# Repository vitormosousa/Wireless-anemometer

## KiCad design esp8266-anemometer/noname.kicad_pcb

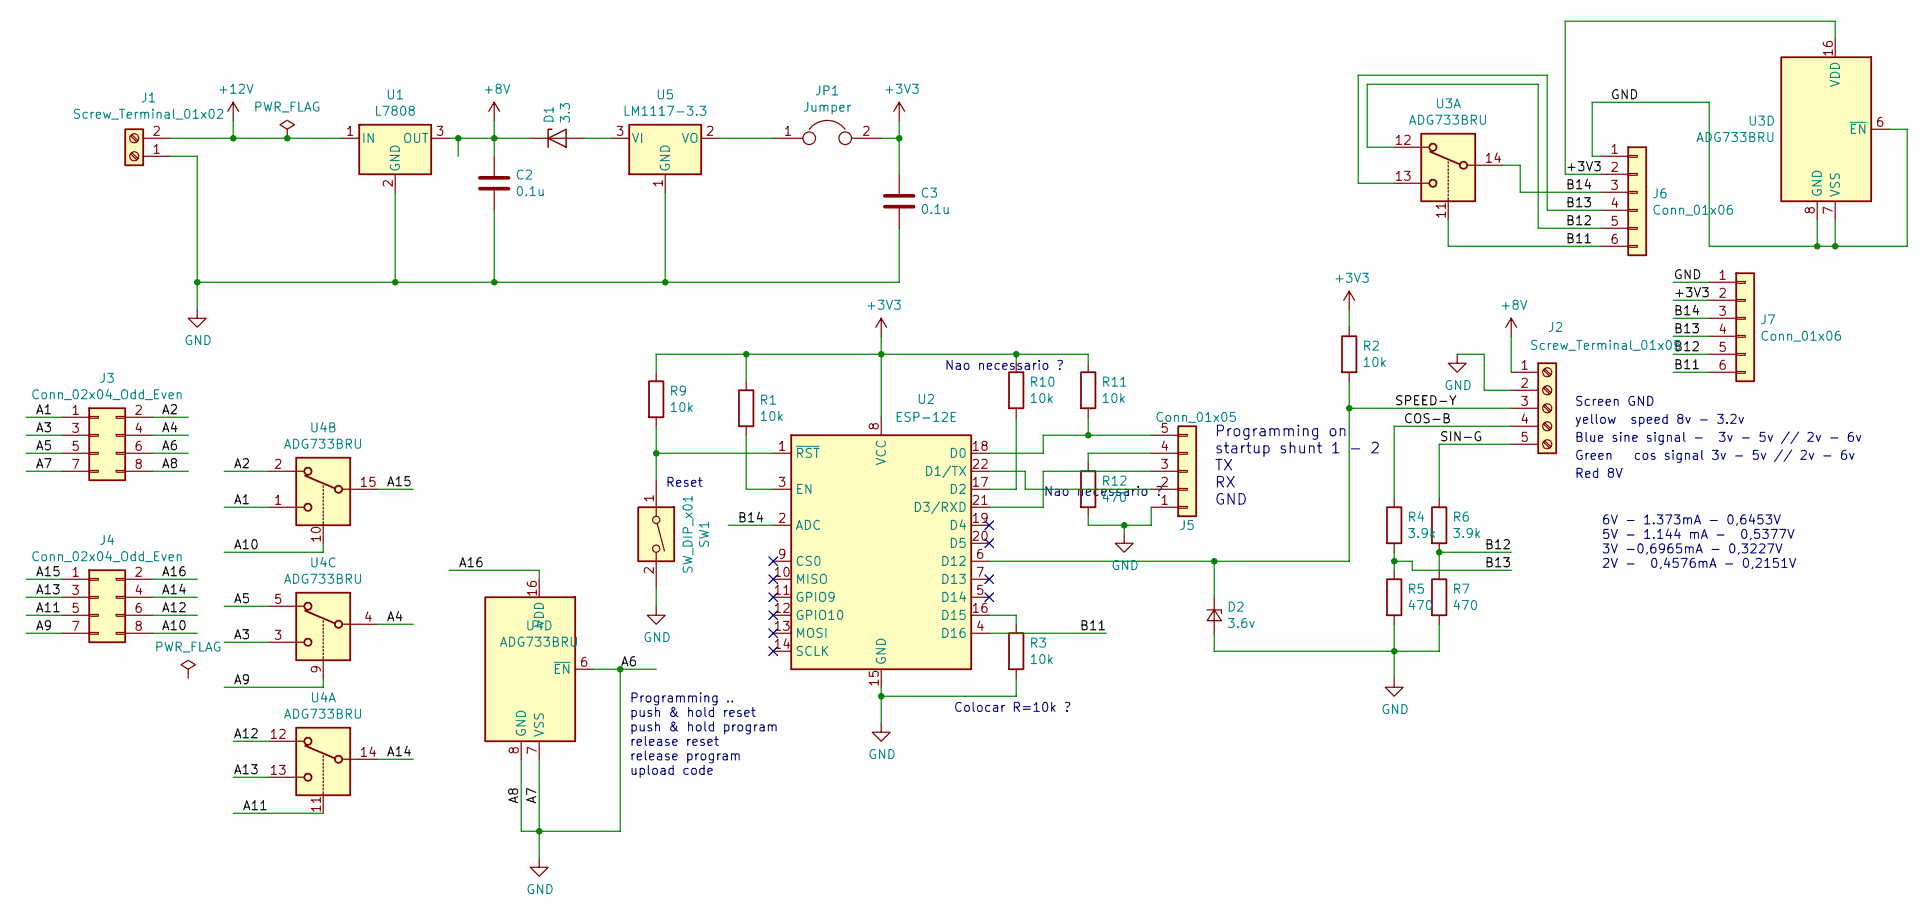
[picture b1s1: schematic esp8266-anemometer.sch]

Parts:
C2, C3: 0.1u; C_Disc_D4.3mm_W1.9mm_P5.00mm
D1: 3.3; D_DO-15_P10.16mm_Horizontal
D2: 3.6v; D_DO-15_P5.08mm_Vertical_AnodeUp
J1: Screw_Terminal_01x02; TerminalBlock_bornier-2_P5.08mm
J2: Screw_Terminal_01x05; TerminalBlock_bornier-5_P5.08mm
J3, J4: Conn_02x04_Odd_Even; PinHeader_2x04_P2.54mm_Vertical
J5: Conn_01x05; PinHeader_1x05_P2.54mm_Vertical
J6, J7: Conn_01x06; PinHeader_1x06_P2.54mm_Vertical
JP1: Jumper; PinHeader_1x02_P2.54mm_Vertical
R1, R10, R11: 10k; R_Axial_DIN0207_L6.3mm_D2.5mm_P10.16mm_Horizontal
R2, R3: 10k; R_Axial_DIN0204_L3.6mm_D1.6mm_P5.08mm_Vertical
R4, R6: 3.9k; R_Axial_DIN0207_L6.3mm_D2.5mm_P10.16mm_Horizontal
R5, R7, R12: 470; R_Axial_DIN0207_L6.3mm_D2.5mm_P10.16mm_Horizontal
R9: 10k; R_Axial_DIN0207_L6.3mm_D2.5mm_P15.24mm_Horizontal
SW1: SW_DIP_x01; SW_PUSH_6mm
U1: L7808; TO-220-3_Vertical
U2: ESP-12E
U3, U4: ADG733BRU; TSSOP-16_4.4x5mm_P0.65mm
U5: LM1117-3.3; TO-220-3_Vertical

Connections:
+8V: C2.1, D1.1 (K), J2.1, U1.3 (OUT)
+12V: J1.2, U1.1 (IN)
/A1: J3.1, U4.1
/A2: J3.2, U4.2
/A3: J3.3, U4.3
/A4: J3.4, U4.4
/A5: J3.5, U4.5
/A9: J4.7, U4.9
/A10: J4.8, U4.10
/A11: J4.5, U4.11
/A12: J4.6, U4.12
/A13: J4.3, U4.13
/A14: J4.4, U4.14
/A15: J4.1, U4.15
/A16: J4.2, U4.16 (VDD)
/B11: J6.6, J7.6, U2.4 (D16), U3.11
/B12: J6.5, J7.5, R6.2, R7.1, U3.12
/B13: J6.4, J7.4, R4.2, R5.1, U3.13
/B14: J6.3, J7.3, U2.2 (ADC), U3.14
/COS-B: J2.4, R4.1
/SIN-G: J2.5, R6.1
/SPEED-Y: D2.1 (K), J2.3, R2.2, U2.6 (D12)
GND: C2.2, C3.2, D2.2 (A), J1.1, J2.2, J3.6, J3.7, J3.8, J5.1, J6.1, J7.1, R3.2, R5.2, R7.2, R12.2, SW1.2, U1.2 (GND), U2.15 (GND), U3.6 (~EN), U3.7 (VSS), U3.8 (GND), U4.6 (~EN), U4.7 (VSS), U4.8 (GND), U5.1 (GND)
unnamed: D1.2 (A), U5.3 (VI)
unnamed: J5.2, U2.22 (D1/TX)
unnamed: J5.3, U2.21 (D3/RXD)
unnamed: J5.4, R12.1
unnamed: J5.5, R11.2, U2.18 (D0)
unnamed: JP1.1, U5.2 (VO)
unnamed: R1.2, U2.3 (EN)
unnamed: R3.1, U2.16 (D15)
unnamed: R9.2, SW1.1, U2.1 (~RST)
unnamed: R10.2, U2.17 (D2)

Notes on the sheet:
Red 8V
Screen GND
Blue sine signal - 3v - 5v // 2v - 6v
Green cos signal 3v - 5v // 2v - 6v
yellow speed 8v - 3.2v
Programming on startup shunt 1 - 2 TX RX GND
Programming .. push & hold reset push & hold program release reset release program upload code
Reset
Colocar R=10k ?
Nao necessario ?
6V - 1.373mA - 0,6453V 5V - 1.144 mA - 0,5377V 3V -0,6965mA - 0,3227V 2V - 0,4576mA - 0,2151V

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
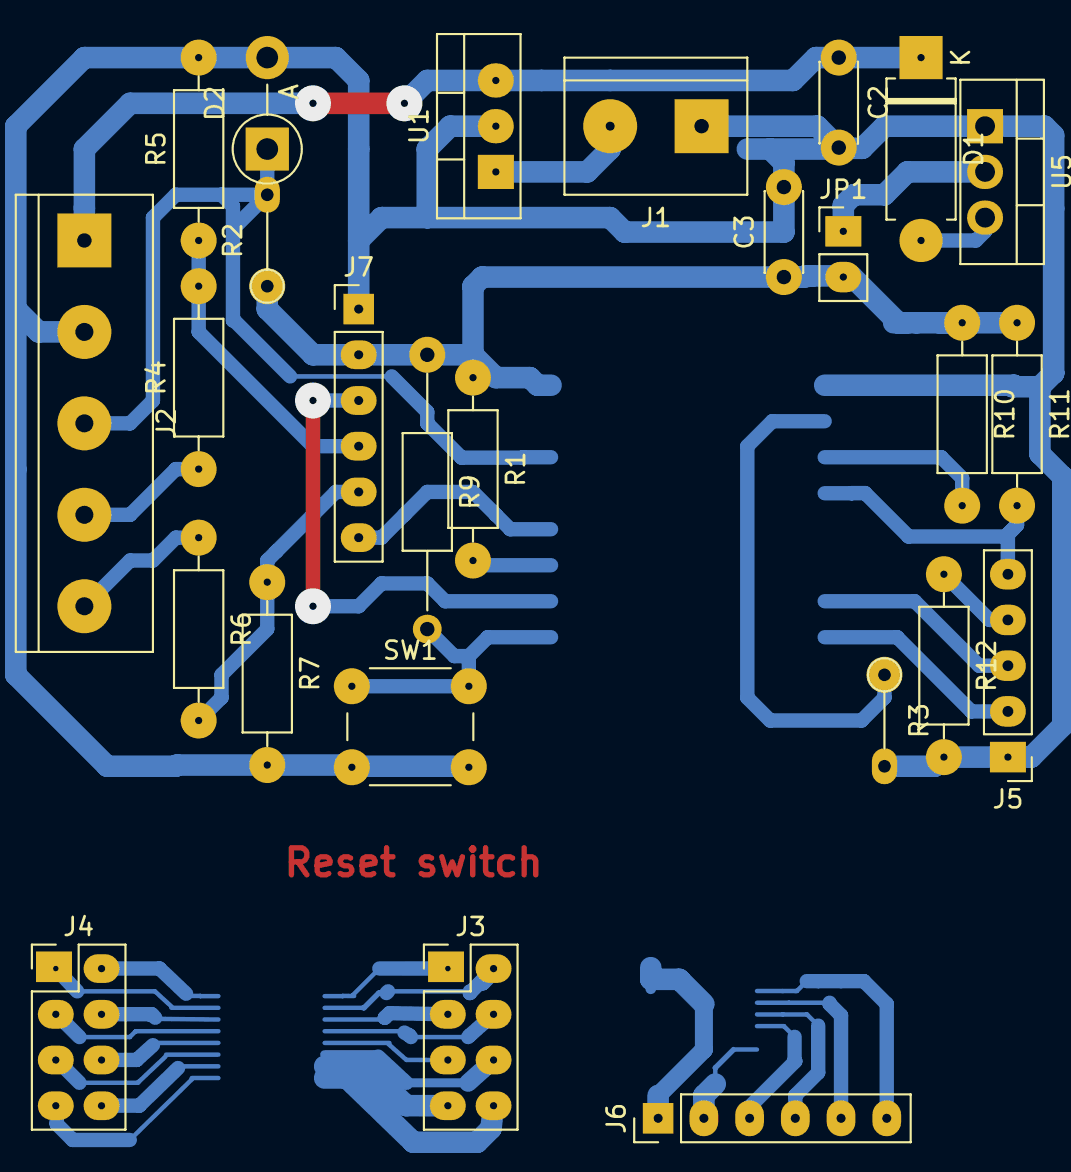
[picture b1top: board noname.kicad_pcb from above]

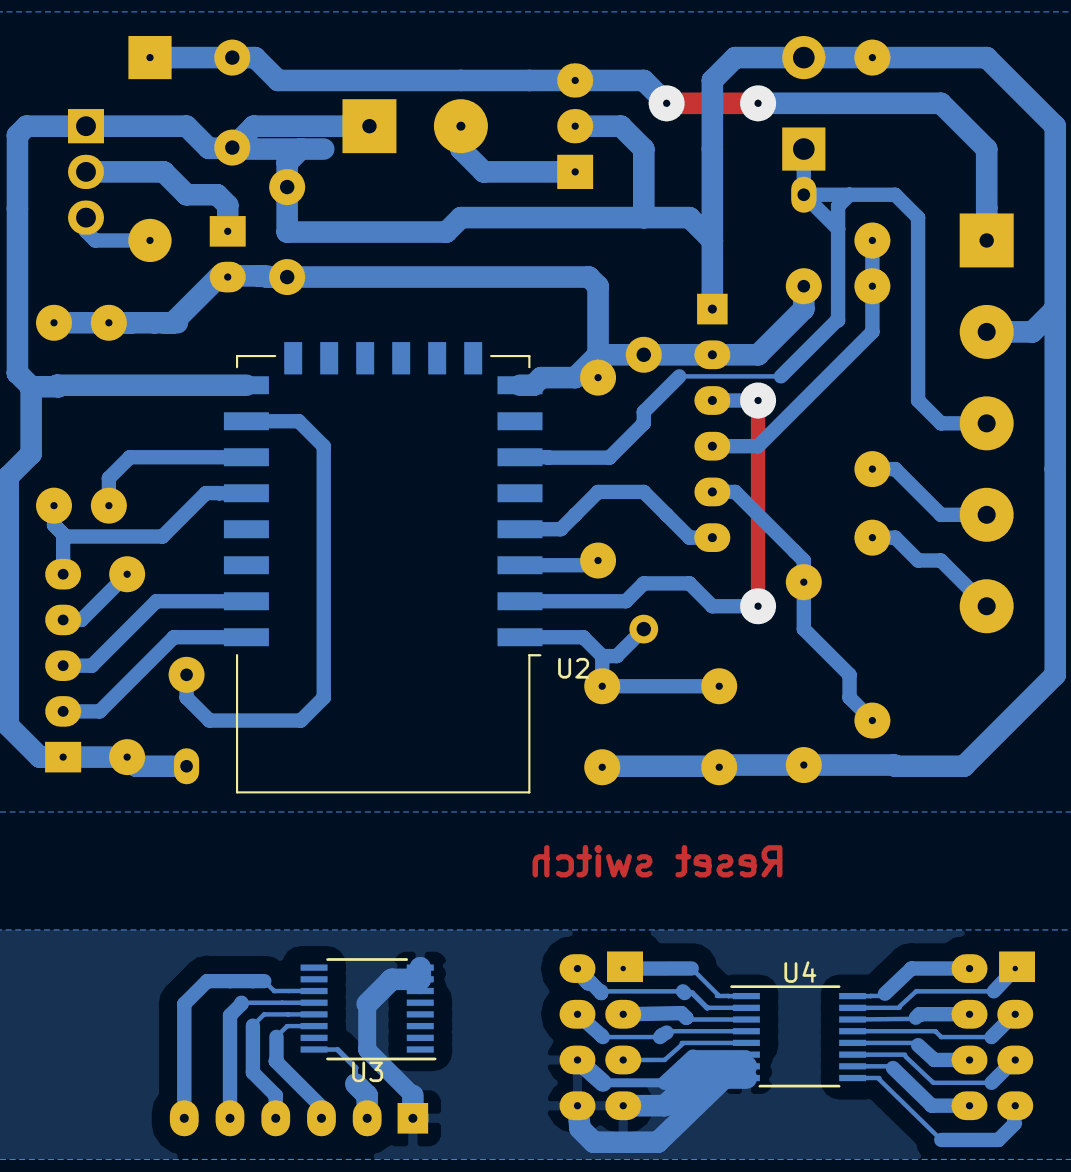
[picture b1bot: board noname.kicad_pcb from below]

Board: 2 copper layers, 29 parts (3 on the bottom side), 35 nets.
